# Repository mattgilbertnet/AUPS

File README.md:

# AUPS

This project has been moved to GitLab: https://gitlab.com/mattgilbertnet/AUPS

Arduino Uno Polulo Shield, made in KiCAD.

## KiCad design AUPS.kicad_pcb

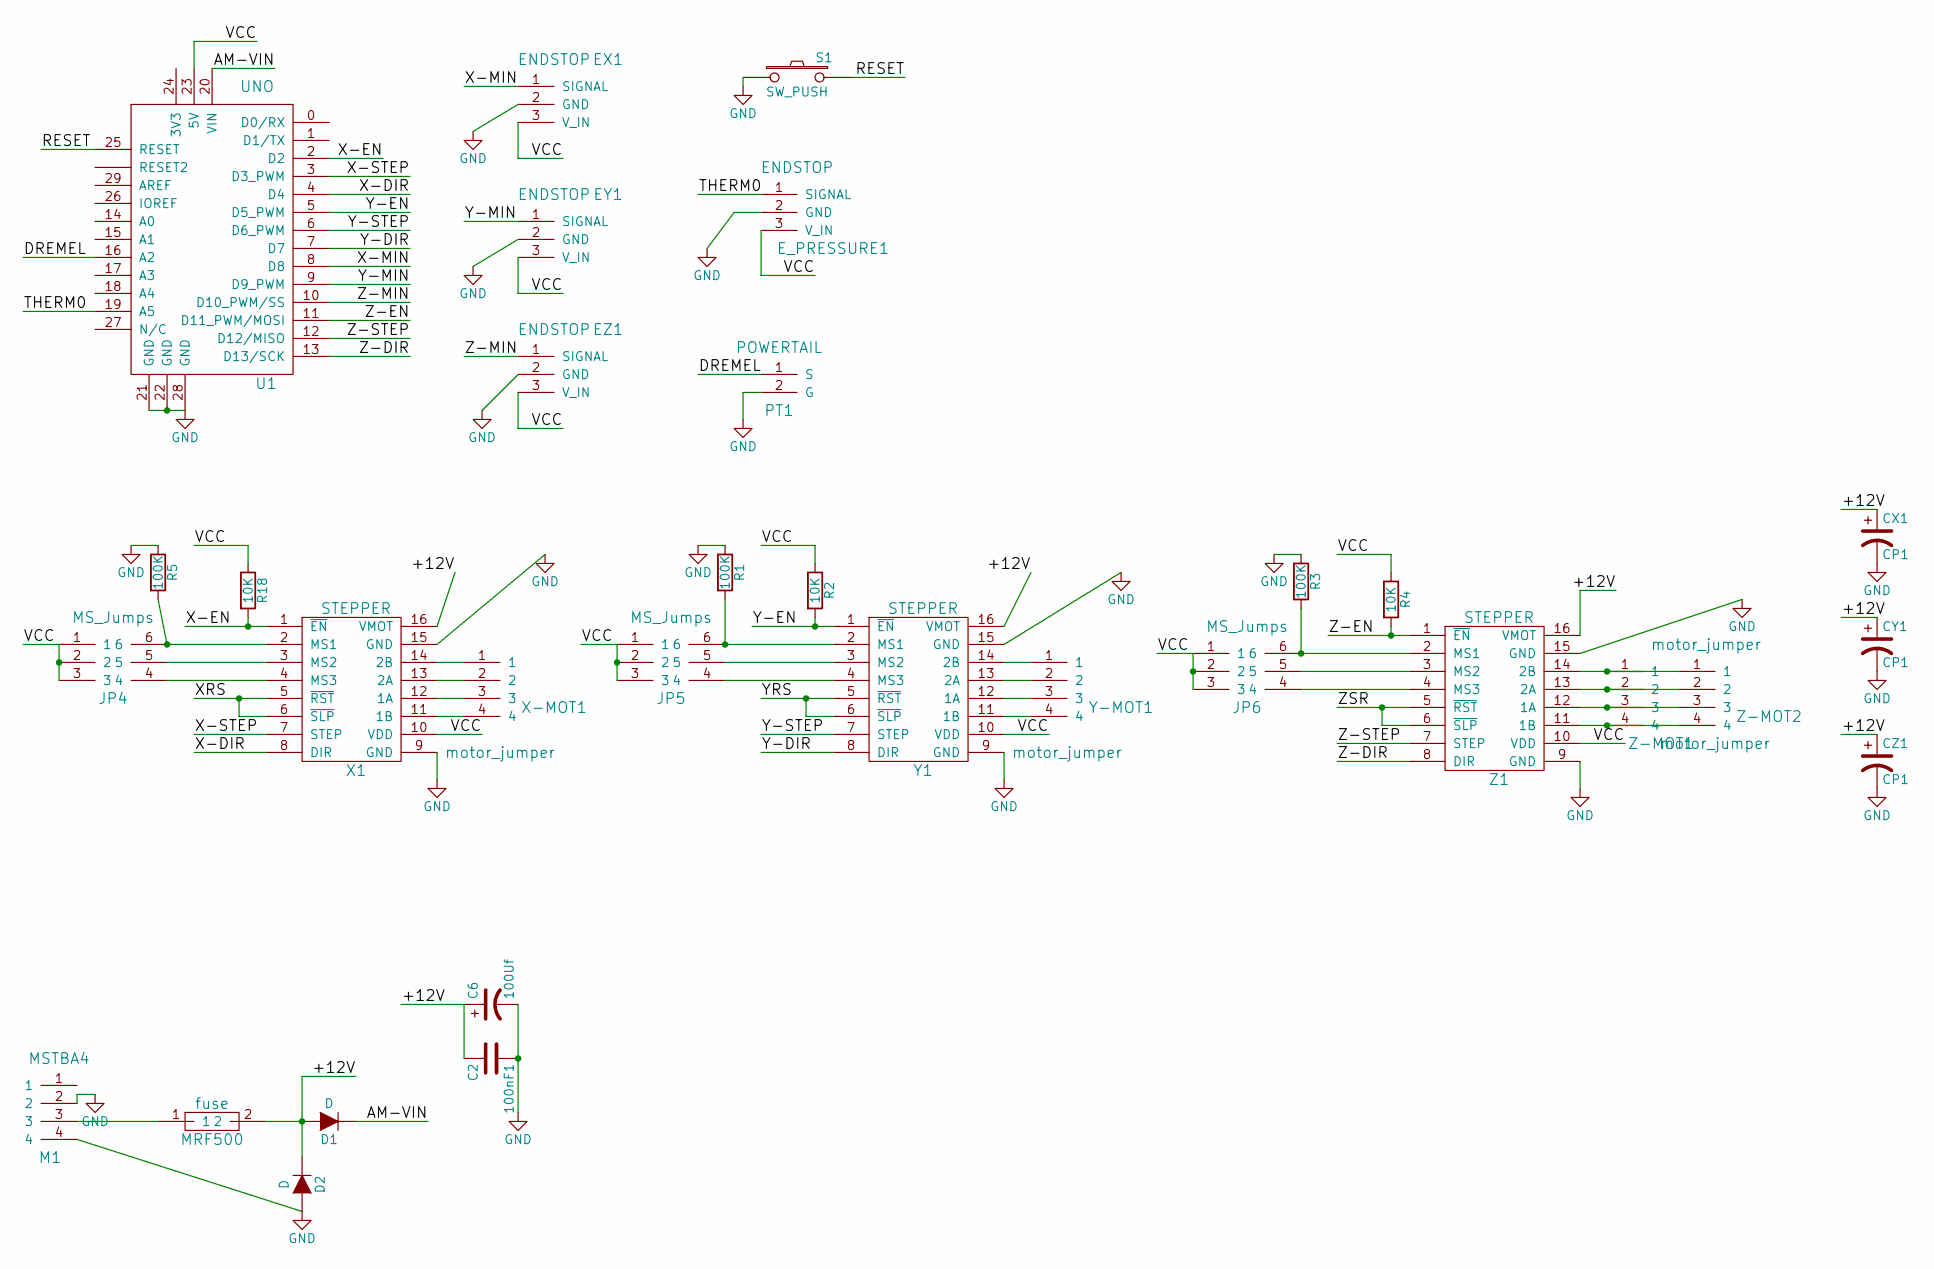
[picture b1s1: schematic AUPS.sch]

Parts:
100nF1: C2; C_Radial_D5_L6_P2.5
C6: 100Uf; C_Radial_D5_L6_P2.5
CX1: CP1; C_Radial_D5_L6_P2.5
CY1: CP1; C_Radial_D5_L6_P2.5
CZ1: CP1; C_Radial_D5_L6_P2.5
D1, D2: D; Diode_DO-41_SOD81_Horizontal_RM10
EX1: ENDSTOP
EY1: ENDSTOP
EZ1: ENDSTOP
E_PRESSURE1: ENDSTOP
JP4, JP5, JP6: MS_Jumps; MS_jumpers
M1: MSTBA4
MRF500: fuse; FUSE
PT1: POWERTAIL
R1, R3, R5: 100K; R_1206_HandSoldering
R2, R4, R18: 10K; R_1206_HandSoldering
S1: SW_PUSH; SW_PUSH_6mm
U1: UNO
X1: STEPPER; Polulo_md09b
X-MOT1: motor_jumper
Y1: STEPPER; Polulo_md09b
Y-MOT1: motor_jumper
Z1: STEPPER; Polulo_md09b
Z-MOT1, Z-MOT2: motor_jumper

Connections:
/+12V: 100nF1.2, C6.1, CX1.1, CY1.1, CZ1.1, D1.2 (A), D2.1 (K), MRF500.2, X1.16 (VMOT), Y1.16 (VMOT), Z1.16 (VMOT)
/AM-VIN: D1.1 (K), U1.20 (VIN)
/DREMEL: PT1.1 (S), U1.16 (A2)
/RESET: S1.2, U1.25 (RESET)
/THERM0: E_PRESSURE1.1 (SIGNAL), U1.19 (A5)
/VCC: EX1.3 (V_IN), EY1.3 (V_IN), EZ1.3 (V_IN), E_PRESSURE1.3 (V_IN), JP4.1, JP4.2, JP4.3, JP5.1, JP5.2, JP5.3, JP6.1, JP6.2, JP6.3, R2.1, R4.1, R18.1, U1.23 (5V), X1.10 (VDD), Y1.10 (VDD), Z1.10 (VDD)
/X-DIR: U1.4 (D4), X1.8 (DIR)
/X-EN: R18.2, U1.2 (D2), X1.1 (~EN)
/X-MIN: EX1.1 (SIGNAL), U1.8 (D8)
/X-STEP: U1.3 (D3_PWM), X1.7 (STEP)
/XRS: X1.5 (~RST), X1.6 (~SLP)
/Y-DIR: U1.7 (D7), Y1.8 (DIR)
/Y-EN: R2.2, U1.5 (D5_PWM), Y1.1 (~EN)
/Y-MIN: EY1.1 (SIGNAL), U1.9 (D9_PWM)
/Y-STEP: U1.6 (D6_PWM), Y1.7 (STEP)
/YRS: Y1.5 (~RST), Y1.6 (~SLP)
/Z-DIR: U1.13 (D13/SCK), Z1.8 (DIR)
/Z-EN: R4.2, U1.11 (D11_PWM/MOSI), Z1.1 (~EN)
/Z-MIN: EZ1.1 (SIGNAL), U1.10 (D10_PWM/SS)
/Z-STEP: U1.12 (D12/MISO), Z1.7 (STEP)
/ZSR: Z1.5 (~RST), Z1.6 (~SLP)
GND: 100nF1.1, C6.2, CX1.2, CY1.2, CZ1.2, D2.2 (A), EX1.2 (GND), EY1.2 (GND), EZ1.2 (GND), E_PRESSURE1.2 (GND), M1.2, M1.4, PT1.2 (G), R1.1, R3.1, R5.1, S1.1, U1.21 (GND), U1.22 (GND), U1.28 (GND), X1.9 (GND), X1.15 (GND), Y1.9 (GND), Y1.15 (GND), Z1.9 (GND), Z1.15 (GND)
unnamed: JP4.4, X1.4 (MS3)
unnamed: JP4.5, X1.3 (MS2)
unnamed: JP4.6, R5.2, X1.2 (MS1)
unnamed: JP5.4, Y1.4 (MS3)
unnamed: JP5.5, Y1.3 (MS2)
unnamed: JP5.6, R1.2, Y1.2 (MS1)
unnamed: JP6.4, Z1.4 (MS3)
unnamed: JP6.5, Z1.3 (MS2)
unnamed: JP6.6, R3.2, Z1.2 (MS1)
unnamed: M1.3, MRF500.1
unnamed: X1.14 (2B), X-MOT1.1
unnamed: X1.13 (2A), X-MOT1.2
unnamed: X1.12 (1A), X-MOT1.3
unnamed: X1.11 (1B), X-MOT1.4
unnamed: Y1.14 (2B), Y-MOT1.1
unnamed: Y1.13 (2A), Y-MOT1.2
unnamed: Y1.12 (1A), Y-MOT1.3
unnamed: Y1.11 (1B), Y-MOT1.4
unnamed: Z1.14 (2B), Z-MOT1.1, Z-MOT2.1
unnamed: Z1.13 (2A), Z-MOT1.2, Z-MOT2.2
unnamed: Z1.12 (1A), Z-MOT1.3, Z-MOT2.3
unnamed: Z1.11 (1B), Z-MOT1.4, Z-MOT2.4

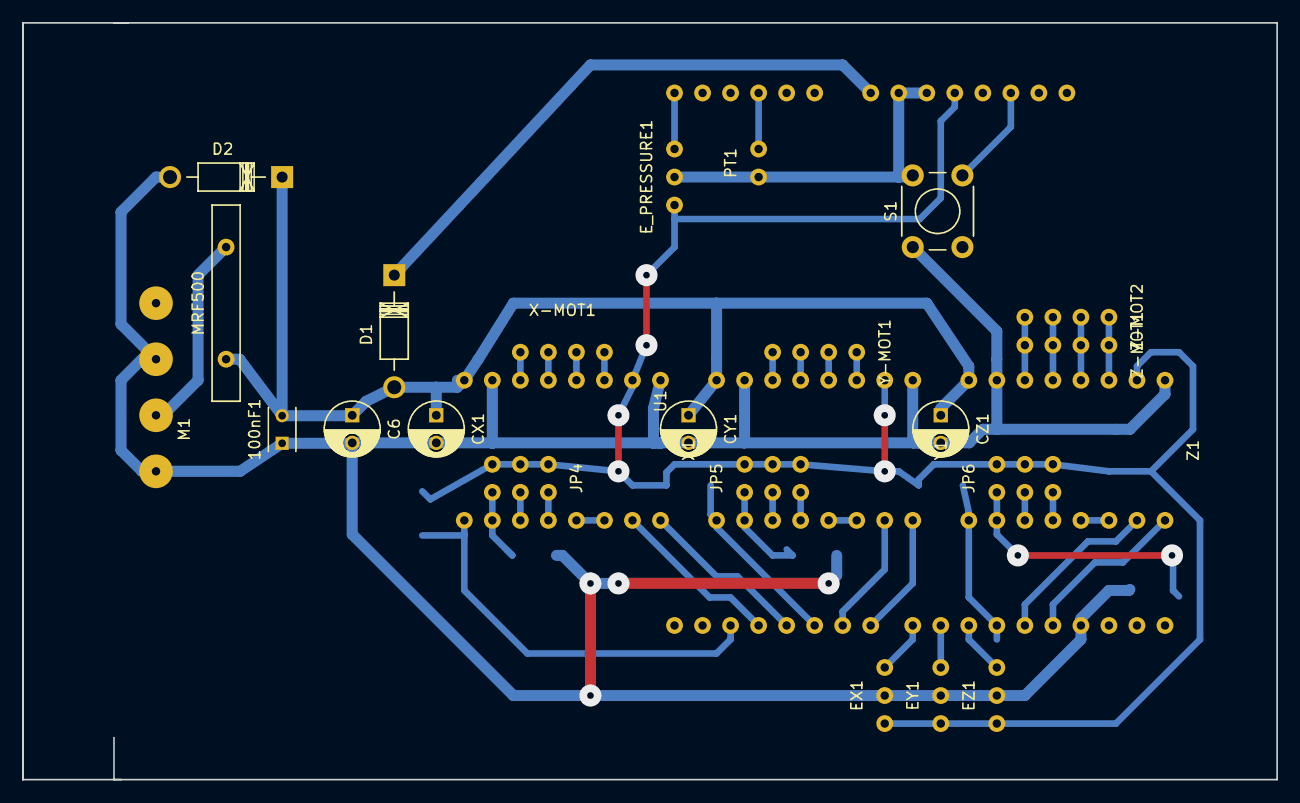
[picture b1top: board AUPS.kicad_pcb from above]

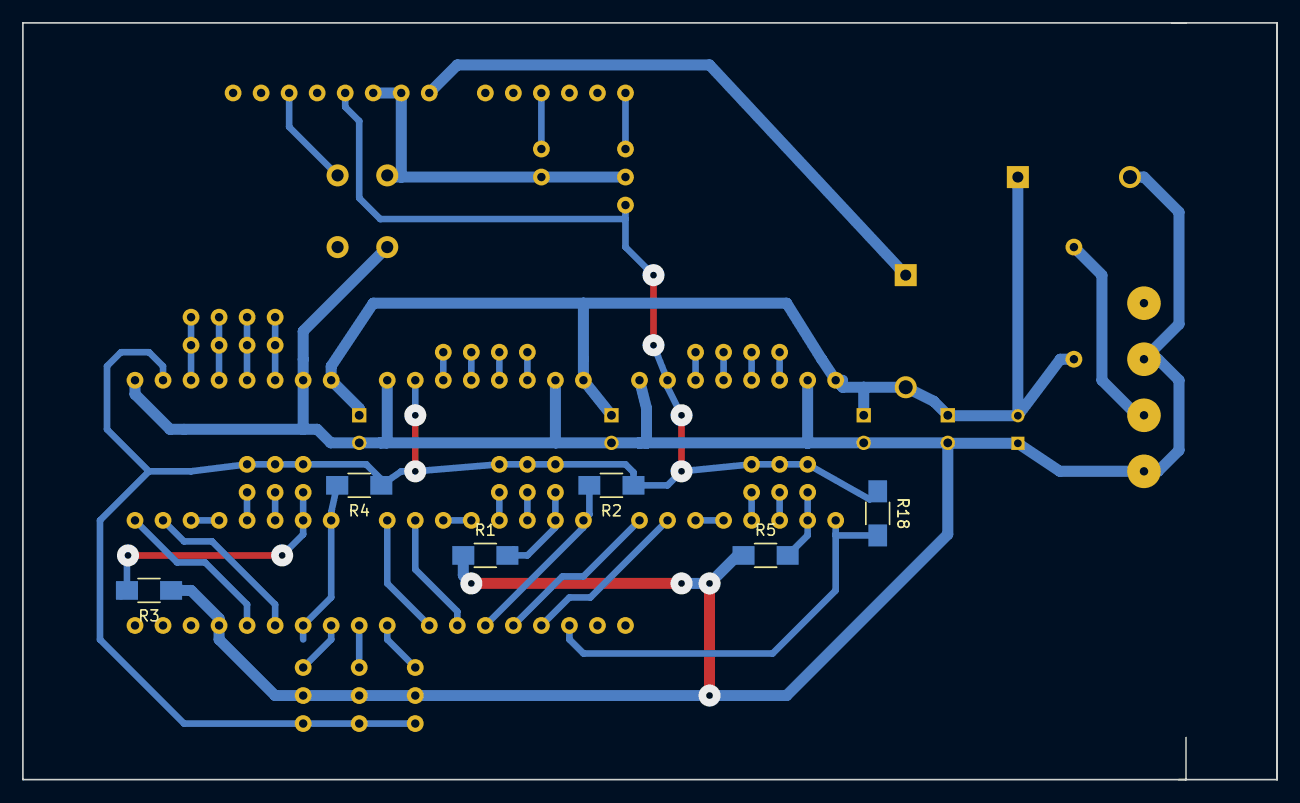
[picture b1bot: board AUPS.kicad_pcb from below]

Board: 2 copper layers, 113.7 x 68.6 mm, 32 parts (6 on the bottom side), 44 nets.
